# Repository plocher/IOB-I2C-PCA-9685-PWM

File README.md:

# IOB-I2C-PCA-9685-PWM
## License: CERN Open Hardware Licence v1.2

IOB I2C PCA9685 PWN driver

### Specifications

 * The PCA9685 is an i2c-controlled PWM driver with a built in free running clock.
 * The board is 5V compliant, which means you can control it from a 3.3V microcontroller and still safely drive up to 6V outputs (for LEDS and Servos)
 * 6 address select pins support up to 62 of these on a single I2C bus
 * Adjustable frequency PWM up to about 1.6 KHz
 * 12-bit resolution for each output
 * Configurable push-pull or open-drain output
 * Output enable pin to quickly disable all the outputs

### Communication Protocol

```C++
Simple I2C 16-bit Reads and Writes:

void I2Cexpander::init9685(uint8_t i2caddr, uint16_t dir) {
    if (i2caddr < base9685) {
        _i2c_address = i2caddr + base9685;
    } else {
        _i2c_address = i2caddr;
    }
    Wire.beginTransmission(_i2c_address);
	Wire.write(PCA9685_MODE1);
	Wire.write(PCA9685_MODE1_SLEEP);
    Wire.endTransmission();  
    delay(1);
    // Set precaler: float prescaleval = ((_oscillator_freq / (freq * 4096.0)) + 0.5) - 1;
    // max 255, min 3
    // internal _oscillator_freq is 25MHz
    Wire.beginTransmission(_i2c_address);
	Wire.write(PCA9685_PRESCALE);
	Wire.write(6);	// a value of 6 is about a 1000 Hz refresh rate  Servos need 60Hz: 101
    Wire.endTransmission();  
    delay(1);
    Wire.beginTransmission(_i2c_address);
	Wire.write(PCA9685_MODE1);
	Wire.write(PCA9685_MODE1_RESTART | PCA9685_MODE1_AUTOINC | PCA9685_MODE1_ALLCALL);
    Wire.endTransmission();  
    delay(1);
    Wire.beginTransmission(_i2c_address);
	Wire.write(PCA9685_MODE2);
	Wire.write(PCA9685_MODE2_TOTEM | PCA9685_MODE2_OEOFF);
    Wire.endTransmission();  
    delay(1);
}

// read uses the config value to distinguish which LED to read/write

uint32_t I2Cexpander::read9685() {
    uint32_t data = 0;
    uint16_t startdata = 0;
    uint16_t stopdata = 0;
    Wire.beginTransmission(_i2c_address);
    Wire.write(PCA9685_BASE_LED0 + (_config * 4));
    int n = Wire.endTransmission(false);  
    if (! ((n == 0) || (n ==7)) ) {
		return (_last);
    }
    Wire.requestFrom(_i2c_address, (uint8_t)4, (uint8_t)1);
    startdata = Wire.read();
    startdata |= (Wire.read() << 8);  
    stopdata = Wire.read();
    stopdata |= (Wire.read() << 8);  
	if (stopdata == startdata)     data = 0;
	else if (stopdata < startdata) data = startdata + stopdata & 0x0FFF;
	else                           data = stopdata - startdata;
    return data;
}

void I2Cexpander::write9685(uint32_t data) {
    /*
     * The chip has a freerunning counter (0..4095, 0x0000 to 0x0FFF)
     * LED#_ON_H/L  bits 0..11 are start 'time' for turn on
     *    Bit 12 (0x1000) means CONSTANT ON, unless OFF bit is also set
     * LED#_OFF_H/L bits 0..11 are start 'time' for turn off
     *    Bit 12 (0x1000) means CONSTANT OFF, overrides any ON setting
     */
    data = data & 0x0FFF;

    //  Stagger starting phase to ensure each string is independent, to reduce power supply spiking
    int start = (_config * 0x0F); // use LED num as beginning count...

    unsigned int end = (data + start) % 0x0FFF;		// 12 bits = 4096
    int b1 = (start     ) & 0x00FF; // low byte ...
    int b2 = (start >> 8) & 0x000F; // ... and high nibble
    int e1 = (end       ) & 0x00FF; // low byte ...
    int e2 = (end   >> 8) & 0x000F; // ... and high nibble

    if (data == 0x0FFF) {		// FULL ON
        b2 |= 0x1000;
    } else if (data == 0x0000) {	// FULL OFF
        e2 |= 0x1000;
    }

    Wire.beginTransmission(_i2c_address);
    Wire.write(PCA9685_BASE_LED0 + (_config * 4));

    Wire.write(b1);  
    Wire.write(b2);  
    Wire.write(e1);  
    Wire.write(e2);  

    Wire.endTransmission();  
}

```

See [I2Cexpander-lib](/pages/I2Cexpander "wikilink") for a more complete interface
library.

### Addressing
The addres selection for the PCA9685 allows for 62 devices, addresses 0x40 to 0x7F.
The board has dip switches for A0 through A5, A6 is hardcoded to "1" in the chip.

**A6**|**A5**|**A4**|**A3**|**A2**|**A1**|**A0**|**ADDRESS (HEX)**
:-----:|:-----:|:-----:|:-----:|:-----:|:-----:|:-----:|:-----:
1|0|0| 0|0|0|0 | 0x40
1|0|0| 0|0|0|1 | 0x41
1|0|0| 0|0|1|0 | 0x42
1|0|0| 0|0|1|1 | 0x43
1|0|0| 0|1|0|0 | 0x44
1|0|0| 0|1|0|1 | 0x45
1|0|0| 0|1|1|0 | 0x46
1|0|0| 0|1|1|1 | 0x47
1|0|0| 1|0|0|0 | 0x48
1|0|0| 1|0|0|1 | 0x49
1|0|0| 1|0|1|0 | 0x4A
1|0|0| 1|0|1|1 | 0x4B
1|0|0| 1|1|0|0 | 0x4C
1|0|0| 1|1|0|1 | 0x4D
1|0|0| 1|1|1|0 | 0x4E
1|0|0| 1|1|1|1 | 0x4F
1|0|1| 0|0|0|0 | 0x50
1|0|1| 0|0|0|1 | 0x51
1|0|1| 0|0|1|0 | 0x52
1|0|1| 0|0|1|1 | 0x53
1|0|1| 0|1|0|0 | 0x54
1|0|1| 0|1|0|1 | 0x55
1|0|1| 0|1|1|0 | 0x56
1|0|1| 0|1|1|1 | 0x57
1|0|1| 1|0|0|0 | 0x58
1|0|1| 1|0|0|1 | 0x59
1|0|1| 1|0|1|0 | 0x5A
1|0|1| 1|0|1|1 | 0x5B
1|0|1| 1|1|0|0 | 0x5C
1|0|1| 1|1|0|1 | 0x5D
1|0|1| 1|1|1|0 | 0x5E
1|0|1| 1|1|1|1 | 0x5F
1|1|0| 0|0|0|0 | 0x60
1|1|0| 0|0|0|1 | 0x61
1|1|0| 0|0|1|0 | 0x62
1|1|0| 0|0|1|1 | 0x63
1|1|0| 0|1|0|0 | 0x64
1|1|0| 0|1|0|1 | 0x65
1|1|0| 0|1|1|0 | 0x66
1|1|0| 0|1|1|1 | 0x67
1|1|0| 1|0|0|0 | 0x68
1|1|0| 1|0|0|1 | 0x69
1|1|0| 1|0|1|0 | 0x6A
1|1|0| 1|0|1|1 | 0x6B
1|1|0| 1|1|0|0 | 0x6C
1|1|0| 1|1|0|1 | 0x6D
1|1|0| 1|1|1|0 | 0x6E
1|1|0| 1|1|1|1 | 0x6F
1|1|1| 0|0|0|0 | 0x70
1|1|1| 0|0|0|1 | 0x71
1|1|1| 0|0|1|0 | 0x72
1|1|1| 0|0|1|1 | 0x73
1|1|1| 0|1|0|0 | 0x74
1|1|1| 0|1|0|1 | 0x75
1|1|1| 0|1|1|0 | 0x76
1|1|1| 0|1|1|1 | 0x77
1|1|1| 1|0|0|0 | 0x78
1|1|1| 1|0|0|1 | 0x79
1|1|1| 1|0|1|0 | 0x7A
1|1|1| 1|0|1|1 | 0x7B
1|1|1| 1|1|0|0 | 0x7C
1|1|1| 1|1|0|1 | 0x7D
1|1|1| 1|1|1|0 | 0x7E
1|1|1| 1|1|1|1 | 0x7F

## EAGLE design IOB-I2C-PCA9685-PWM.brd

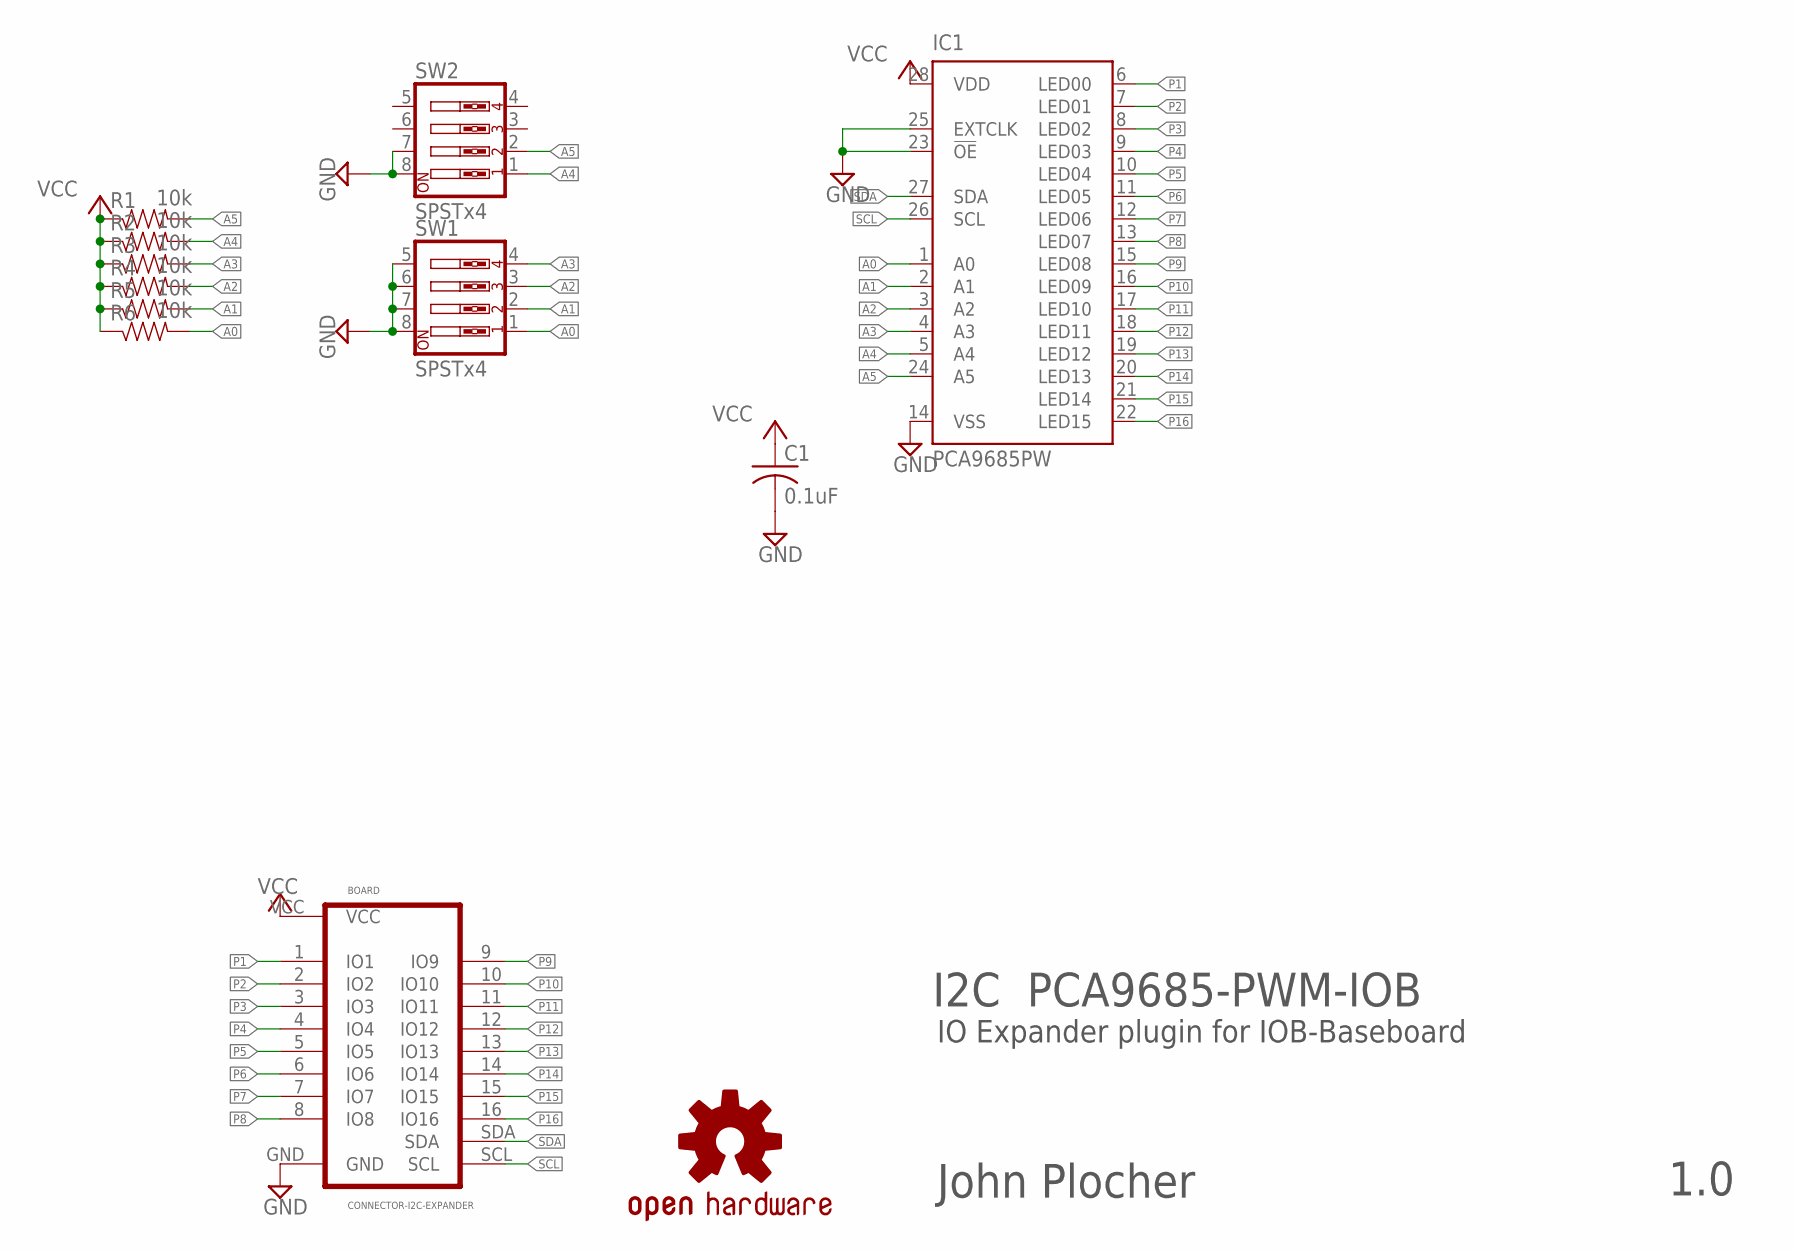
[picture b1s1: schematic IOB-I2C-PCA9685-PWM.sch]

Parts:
BOARD: CONNECTOR-I2C-EXPANDER; I2C-EXPANDER
C1: 0.1uF; 0603-CAP
IC1: PCA9685PW; TSSOP28
R1, R2, R3, R4, R5, R6: 10k; 0603-RES
SW1, SW2: SPSTx4; EDG-04
U$1: OSHW; OSHW-LOGO-L

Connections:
A0: IC1.1 (A0), R6.2, SW1.1
A1: IC1.2 (A1), R5.2, SW1.2
A2: IC1.3 (A2), R4.2, SW1.3
A3: IC1.4 (A3), R3.2, SW1.4
A4: IC1.5 (A4), R2.2, SW2.1
A5: IC1.24 (A5), R1.2, SW2.2
GND: BOARD.GND, C1.2, IC1.14 (VSS), IC1.23 (!OE), IC1.25 (EXTCLK), SW1.5, SW1.6, SW1.7, SW1.8, SW2.7, SW2.8
P1: BOARD.1 (IO1), IC1.6 (LED00)
P2: BOARD.2 (IO2), IC1.7 (LED01)
P3: BOARD.3 (IO3), IC1.8 (LED02)
P4: BOARD.4 (IO4), IC1.9 (LED03)
P5: BOARD.5 (IO5), IC1.10 (LED04)
P6: BOARD.6 (IO6), IC1.11 (LED05)
P7: BOARD.7 (IO7), IC1.12 (LED06)
P8: BOARD.8 (IO8), IC1.13 (LED07)
P9: BOARD.9 (IO9), IC1.15 (LED08)
P10: BOARD.10 (IO10), IC1.16 (LED09)
P11: BOARD.11 (IO11), IC1.17 (LED10)
P12: BOARD.12 (IO12), IC1.18 (LED11)
P13: BOARD.13 (IO13), IC1.19 (LED12)
P14: BOARD.14 (IO14), IC1.20 (LED13)
P15: BOARD.15 (IO15), IC1.21 (LED14)
P16: BOARD.16 (IO16), IC1.22 (LED15)
SCL: BOARD.SCL, IC1.26 (SCL)
SDA: BOARD.SDA, IC1.27 (SDA)
VCC: BOARD.VCC, C1.1, IC1.28 (VDD), R1.1, R2.1, R3.1, R4.1, R5.1, R6.1

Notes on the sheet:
I2C PCA9685-PWM-IOB
IO Expander plugin for IOB-Baseboard
John Plocher
1.0

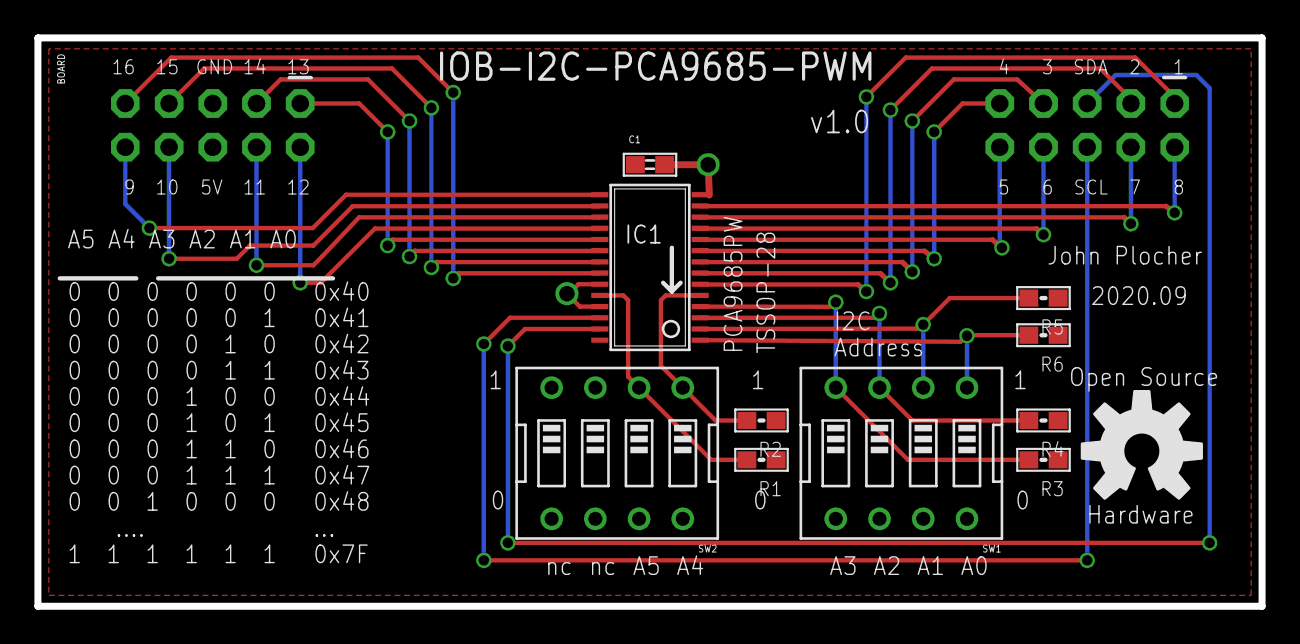
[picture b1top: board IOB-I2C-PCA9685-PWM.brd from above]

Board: 2 copper layers, 71.1 x 33.0 mm, 12 parts (0 on the bottom side), 26 nets.

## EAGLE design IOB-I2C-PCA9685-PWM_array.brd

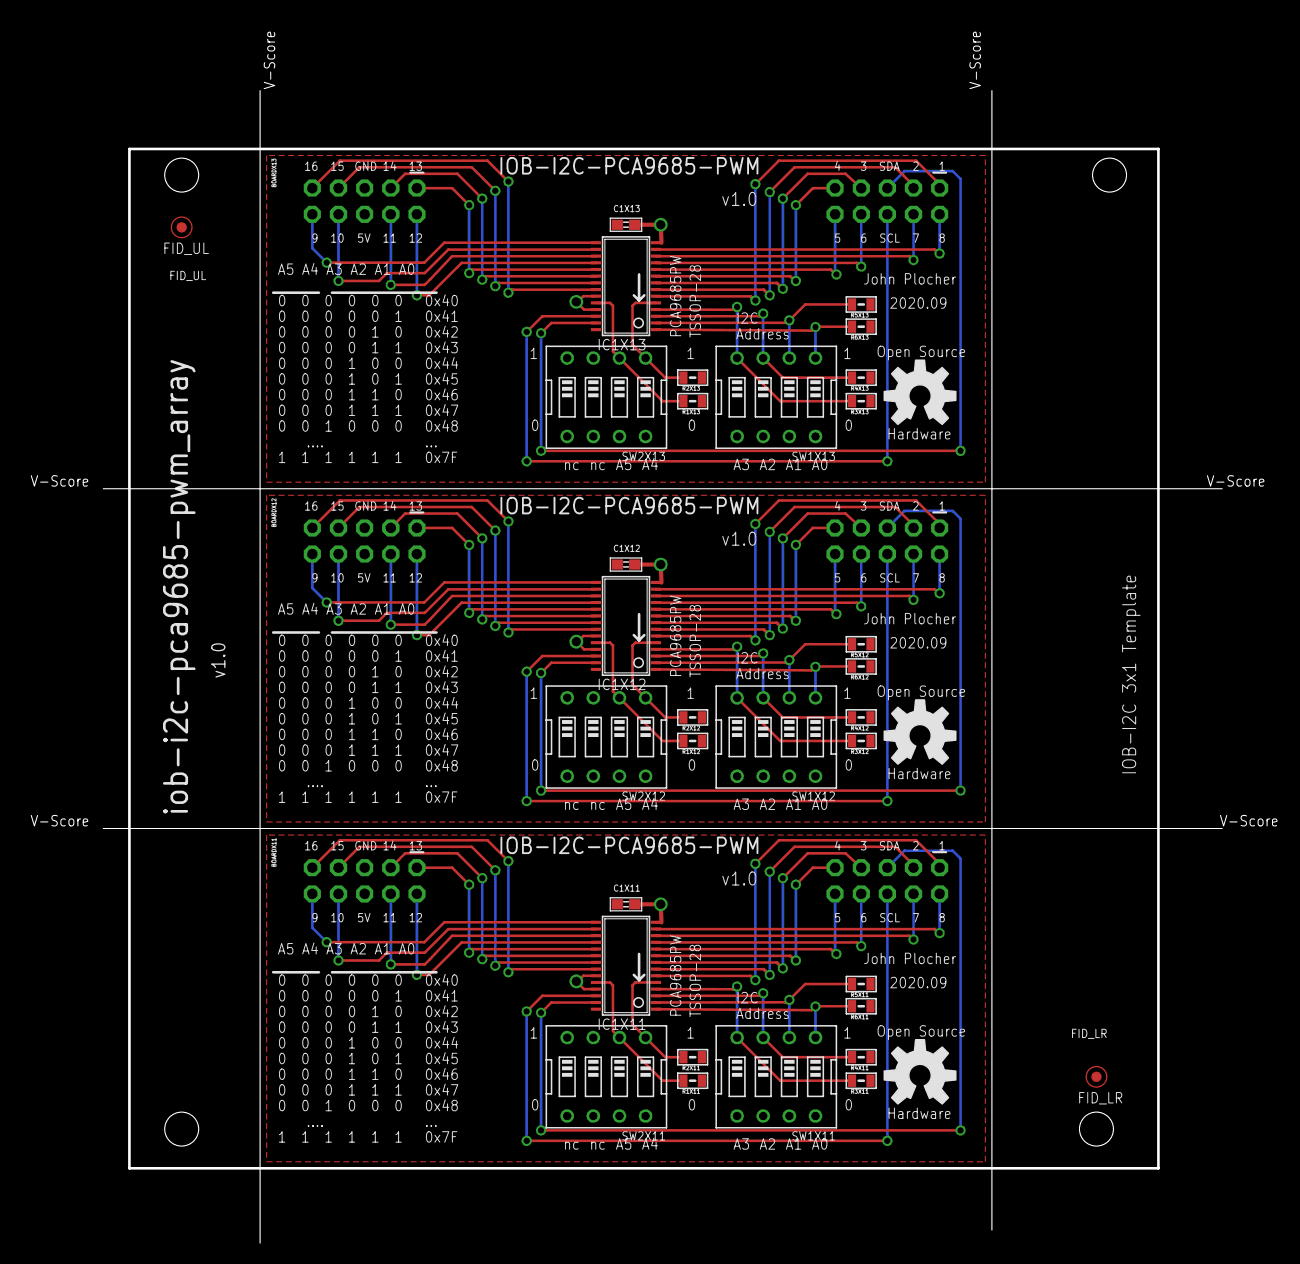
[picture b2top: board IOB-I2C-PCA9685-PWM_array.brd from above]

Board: 2 copper layers, 122.1 x 118.6 mm, 39 parts (0 on the bottom side), 78 nets.

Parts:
BOARDX11, BOARDX12, BOARDX13: CONNECTOR-I2C-EXPANDER; I2C-EXPANDER
C1X11, C1X12, C1X13: 0.1uF; 0603-CAP
FID_LR: FIDUCIAL; FIDUCIAL_1MM
FID_UL: FIDUCIAL; FIDUCIAL_1MM
IC1X11, IC1X12, IC1X13: PCA9685PW; TSSOP28
R1X11, R1X12, R1X13, R2X11, R2X12, R2X13, R3X11, R3X12, R3X13, R4X11, R4X12, R4X13, R5X11, R5X12, R5X13, R6X11, R6X12, R6X13: 10k; 0805-RES
SW1X11, SW1X12, SW1X13, SW2X11, SW2X12, SW2X13: SPSTx4; EDG-04
U$1X11, U$1X12, U$1X13: OSHW; OSHW-LOGO-L
U$5X1: BOARD; BOARD-TEMPLATE-IOB-I2C-3X1-ARRAY

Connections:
A0X11: IC1X11.1, R6X11.2, SW1X11.1
A0X12: IC1X12.1, R6X12.2, SW1X12.1
A0X13: IC1X13.1, R6X13.2, SW1X13.1
A1X11: IC1X11.2, R5X11.2, SW1X11.2
A1X12: IC1X12.2, R5X12.2, SW1X12.2
A1X13: IC1X13.2, R5X13.2, SW1X13.2
A2X11: IC1X11.3, R4X11.2, SW1X11.3
A2X12: IC1X12.3, R4X12.2, SW1X12.3
A2X13: IC1X13.3, R4X13.2, SW1X13.3
A3X11: IC1X11.4, R3X11.2, SW1X11.4
A3X12: IC1X12.4, R3X12.2, SW1X12.4
A3X13: IC1X13.4, R3X13.2, SW1X13.4
A4X11: IC1X11.5, R2X11.2, SW2X11.1
A4X12: IC1X12.5, R2X12.2, SW2X12.1
A4X13: IC1X13.5, R2X13.2, SW2X13.1
A5X11: IC1X11.24, R1X11.2, SW2X11.2
A5X12: IC1X12.24, R1X12.2, SW2X12.2
A5X13: IC1X13.24, R1X13.2, SW2X13.2
GNDX11: BOARDX11.GND, C1X11.2, IC1X11.14, IC1X11.23, IC1X11.25, SW1X11.5, SW1X11.6, SW1X11.7, SW1X11.8, SW2X11.7, SW2X11.8
GNDX12: BOARDX12.GND, C1X12.2, IC1X12.14, IC1X12.23, IC1X12.25, SW1X12.5, SW1X12.6, SW1X12.7, SW1X12.8, SW2X12.7, SW2X12.8
GNDX13: BOARDX13.GND, C1X13.2, IC1X13.14, IC1X13.23, IC1X13.25, SW1X13.5, SW1X13.6, SW1X13.7, SW1X13.8, SW2X13.7, SW2X13.8
P1X11: BOARDX11.1, IC1X11.6
P1X12: BOARDX12.1, IC1X12.6
P1X13: BOARDX13.1, IC1X13.6
P2X11: BOARDX11.2, IC1X11.7
P2X12: BOARDX12.2, IC1X12.7
P2X13: BOARDX13.2, IC1X13.7
P3X11: BOARDX11.3, IC1X11.8
P3X12: BOARDX12.3, IC1X12.8
P3X13: BOARDX13.3, IC1X13.8
P4X11: BOARDX11.4, IC1X11.9
P4X12: BOARDX12.4, IC1X12.9
P4X13: BOARDX13.4, IC1X13.9
P5X11: BOARDX11.5, IC1X11.10
P5X12: BOARDX12.5, IC1X12.10
P5X13: BOARDX13.5, IC1X13.10
P6X11: BOARDX11.6, IC1X11.11
P6X12: BOARDX12.6, IC1X12.11
P6X13: BOARDX13.6, IC1X13.11
P7X11: BOARDX11.7, IC1X11.12
P7X12: BOARDX12.7, IC1X12.12
P7X13: BOARDX13.7, IC1X13.12
P8X11: BOARDX11.8, IC1X11.13
P8X12: BOARDX12.8, IC1X12.13
P8X13: BOARDX13.8, IC1X13.13
P9X11: BOARDX11.9, IC1X11.15
P9X12: BOARDX12.9, IC1X12.15
P9X13: BOARDX13.9, IC1X13.15
P10X11: BOARDX11.10, IC1X11.16
P10X12: BOARDX12.10, IC1X12.16
P10X13: BOARDX13.10, IC1X13.16
P11X11: BOARDX11.11, IC1X11.17
P11X12: BOARDX12.11, IC1X12.17
P11X13: BOARDX13.11, IC1X13.17
P12X11: BOARDX11.12, IC1X11.18
P12X12: BOARDX12.12, IC1X12.18
P12X13: BOARDX13.12, IC1X13.18
P13X11: BOARDX11.13, IC1X11.19
P13X12: BOARDX12.13, IC1X12.19
P13X13: BOARDX13.13, IC1X13.19
P14X11: BOARDX11.14, IC1X11.20
P14X12: BOARDX12.14, IC1X12.20
P14X13: BOARDX13.14, IC1X13.20
P15X11: BOARDX11.15, IC1X11.21
P15X12: BOARDX12.15, IC1X12.21
P15X13: BOARDX13.15, IC1X13.21
P16X11: BOARDX11.16, IC1X11.22
P16X12: BOARDX12.16, IC1X12.22
P16X13: BOARDX13.16, IC1X13.22
SCLX11: BOARDX11.SCL, IC1X11.26
SCLX12: BOARDX12.SCL, IC1X12.26
SCLX13: BOARDX13.SCL, IC1X13.26
SDAX11: BOARDX11.SDA, IC1X11.27
SDAX12: BOARDX12.SDA, IC1X12.27
SDAX13: BOARDX13.SDA, IC1X13.27
VCCX11: BOARDX11.VCC, C1X11.1, IC1X11.28, R1X11.1, R2X11.1, R3X11.1, R4X11.1, R5X11.1, R6X11.1
VCCX12: BOARDX12.VCC, C1X12.1, IC1X12.28, R1X12.1, R2X12.1, R3X12.1, R4X12.1, R5X12.1, R6X12.1
VCCX13: BOARDX13.VCC, C1X13.1, IC1X13.28, R1X13.1, R2X13.1, R3X13.1, R4X13.1, R5X13.1, R6X13.1

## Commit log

2020-09-11 Initial version
2020-09-11 fixed naming style
2020-09-11 update docs
2020-09-18 added Graphic
2020-10-05 added values for connectors
2020-10-06 normalized values

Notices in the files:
parts and their libraries:
SPCoast: http://freedomdefined.org/OSHW Creative Commons - Attribution - ShareAlike 3.0
